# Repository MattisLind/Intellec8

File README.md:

# Intellec8

I bought this Intellec 8/80 on a fleamarket outside Stockholm 30 years ago for the equivalent of ten euros. It has been sitting on a shelf since then and now I got the inspiration to fix it. Before doing anything with the machine I dumed the [firmware](https://github.com/MattisLind/Intellec8/tree/main/EPROMImages) of the EPROMs. 16 1702 EPROM chips. Each of them containing 256 bytes of non-volatile storage. Then I dismantled the entire machine in to pieces and cleaned some 40 years of dust from it. Meanwhile I took quite a lot of photos of the various parts and puth in the [Pictures folder](https://github.com/MattisLind/Intellec8/tree/main/Pictures). 

The first thing to check were the PSU. The Intellec 8 has three PSU assemblies. One provides +5V, another provide +/- 12V and the last one provide -9V and AC for the programming voltage. The -9V supply and the +/- 12V supply worked just fine.

The first thing I tested was the little crowbar addon board. It tripped at almost 9V, a bit to much in my taste, but it was possible to adjust it down to 5.7V. There didn't seemed to be any problems with that other than it was not set correctly.

Then I started working with the PSUs. All off them worked fine except for the +5V PSU that didn't regulate well at all. I had to turn off the crowbare not to make it trip every time. Evverything measured fine, capacitors, carbon composite resistors, forward drop over semiconductor PN-junctions. But it didn't regulate well. Tried to replace the LM723 regulator IC with a NOS IC. But no difference. Then I looked more on the power transistor that acted as a driver for the output stage of the regulator. It was very leaky. With a new power transistor in place the PSU worked fine.

I installed the Front panel controller, CPU and the three memory boards in the backplane and attached the flat cables from the front panel to the front panel controller board and turne the power switch on. There were some kind of activity on the front panel. I could examine and deposit into memory, but RUN mode behaved odd. I wasn't able to single step the CPU but the RUN light could come on. But in RUN mode there were no activity on the FETCH indicator. Strange.

I checked all LEDs on the panel and they seemed to work find as did the switches. To trace problems further I needed to meausure on the front panel controller board. That was quite tricky with the board installed in the backplane. I needed an extender card. So I sat down one Saturday and designed one.

I also inclued test point so it would be easier to attach a logic analyzer if that turned out to be necessary. The more test points the better. And a lot of ground points to be able to attache the ground probes of the LA.

A few weeks later the boards arrived and so did the connector. I choosen a wire-wrap connector which i bent the legs a bit on to make a sturdy connection between the board and the connector.

Now I hade the possibiliy to probe around on the board. The FETCH cycle signal toggled all the time but still the LED was dark. The signal went through a 7417 OC buffer, A3. It turned out that it was always high on the output. A low will cause the LED to be lit. A high will cause it to be turned off. Removed it and tested in my Retro Chip Tester and, yes, it tested bad. A new (date code 1971), tested 7417, was installed and the front panel was a lot happier.

I could enter a short loop at address 0 that was looping back to itself and also single step this little program. Nice!

But when checking the memory at 3800h where the monitor was supposed be located were very strange and did not match the content of the previouslt dumped EPROMs. Pulled out the EPROM board from the backplane and immediatelty saw something that made me suspicous. Two DIP-swicthes. I have had problmes with DIP-switches in the past. And sure enough, closed switches read open-circuit on the meter. Tried to exercise the switches. Tried deoxit, which made it worse. In the end I had to replace them and then with new swicthes in place the memory at 3800h was accessible. I could even start the monitor and saw the LED indicate I/O acces which was likely to be the monitor polling the UART for incoming character.

Now I just have create a current loop adapter and test the I/O card.

## Modifications to support FACIT paper tape reader and punch

```
3639                          .ORG   3639h   
3639   3E FA        RDR:      MVI   A,0FAH   
363B   D3 05                  OUT   5   
363D   DB 05        RLO:      IN    5   
363F   1F                     RAR   
3640   1F                     RAR   
3641   1F                     RAR   
3642   D8                     RC   
3643   17                     RAL   
3644   DA 3D 36               JC    RLO   
3647   DB 04                  IN    4   
3649   F5                     PUSH  PSW   
364A   3E FB                  MVI   A,0FBH   
364C   D3 05                  OUT   5   
364E   DB 05        RHI:      IN    5   
3650   E6 02                  ANI   02H   
3652   CA 4E 36               JZ    RHI   
3655   F1                     POP   PSW   
3656   2F                     CMA   
3657   B7                     ORA   A   
3658   C9                     RET   
3659                PUNCH:    
3659   DB 05                  IN    5   
365B   E6 10                  ANI   010H   
365D   C2 59 36               JNZ   PUNCH   
3660   79                     MOV   A,C   
3661   2F                     CMA   
3662   D3 04                  OUT   4   
3664   3E AF                  MVI   A,0AFH   
3666   D3 05                  OUT   5   
3668   DB 05        HIGH:     IN    5   
366A   E6 10                  ANI   010H   
366C   CA 68 36               JZ    HIGH   
366F   3E BF                  MVI   A,0BFH   
3671   D3 05                  OUT   5   
3673   C9                     RET   
```
Jumptable-locatation at 3010 need change to 59H.

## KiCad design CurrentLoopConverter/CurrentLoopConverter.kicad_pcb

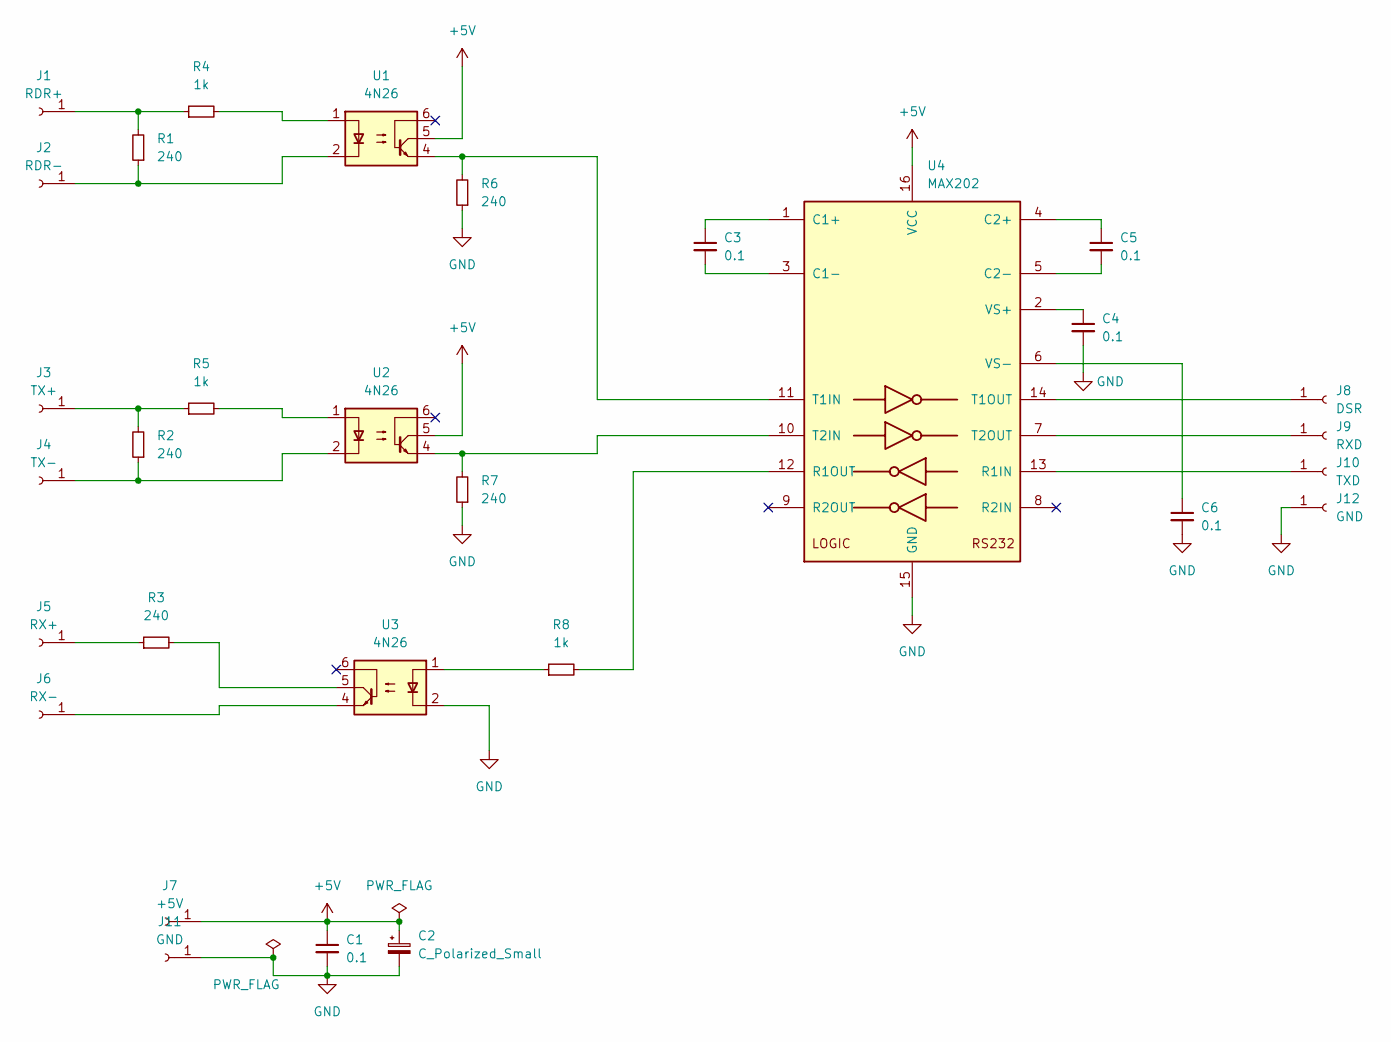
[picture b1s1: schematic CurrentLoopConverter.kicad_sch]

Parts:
C1, C3, C4, C5, C6: 0.1; C_Rect_L7.0mm_W2.0mm_P5.00mm
C2: C_Polarized_Small; CP_Radial_D5.0mm_P2.50mm
J1: RDR+; PinHeader_1x01_P2.54mm_Vertical
J2: RDR-; PinHeader_1x01_P2.54mm_Vertical
J3: TX+; PinHeader_1x01_P2.54mm_Vertical
J4: TX-; PinHeader_1x01_P2.54mm_Vertical
J5: RX+; PinHeader_1x01_P2.54mm_Vertical
J6: RX-; PinHeader_1x01_P2.54mm_Vertical
J7: +5V; PinHeader_1x01_P2.54mm_Vertical
J8: DSR; PinHeader_1x01_P2.54mm_Vertical
J9: RXD; PinHeader_1x01_P2.54mm_Vertical
J10: TXD; PinSocket_1x01_P2.54mm_Vertical
J11, J12: GND; PinHeader_1x01_P2.54mm_Vertical
R1, R2, R3, R6, R7: 240; R_Axial_DIN0207_L6.3mm_D2.5mm_P10.16mm_Horizontal
R4, R5, R8: 1k; R_Axial_DIN0207_L6.3mm_D2.5mm_P10.16mm_Horizontal
U1, U2, U3: 4N26; DIP-6_W7.62mm
U4: MAX202; DIP-16_W7.62mm

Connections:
+5V: C1.1, C2.1, J7.1, U1.5, U2.5, U4.16 (VCC)
GND: C1.2, C2.2, C4.2, C6.2, J11.1, J12.1, R6.1, R7.1, U3.2, U4.15 (GND)
unnamed: C3.1, U4.1 (C1+)
unnamed: C3.2, U4.3 (C1-)
unnamed: C4.1, U4.2 (VS+)
unnamed: C5.1, U4.4 (C2+)
unnamed: C5.2, U4.5 (C2-)
unnamed: C6.1, U4.6 (VS-)
unnamed: J1.1, R1.2, R4.1
unnamed: J2.1, R1.1, U1.2
unnamed: J3.1, R2.2, R5.1
unnamed: J4.1, R2.1, U2.2
unnamed: J5.1, R3.1
unnamed: J6.1, U3.4
unnamed: J8.1, U4.14 (T1OUT)
unnamed: J9.1, U4.7 (T2OUT)
unnamed: J10.1, U4.13 (R1IN)
unnamed: R3.2, U3.5
unnamed: R4.2, U1.1
unnamed: R5.2, U2.1
unnamed: R6.2, U1.4, U4.11 (T1IN)
unnamed: R7.2, U2.4, U4.10 (T2IN)
unnamed: R8.1, U3.1
unnamed: R8.2, U4.12 (R1OUT)

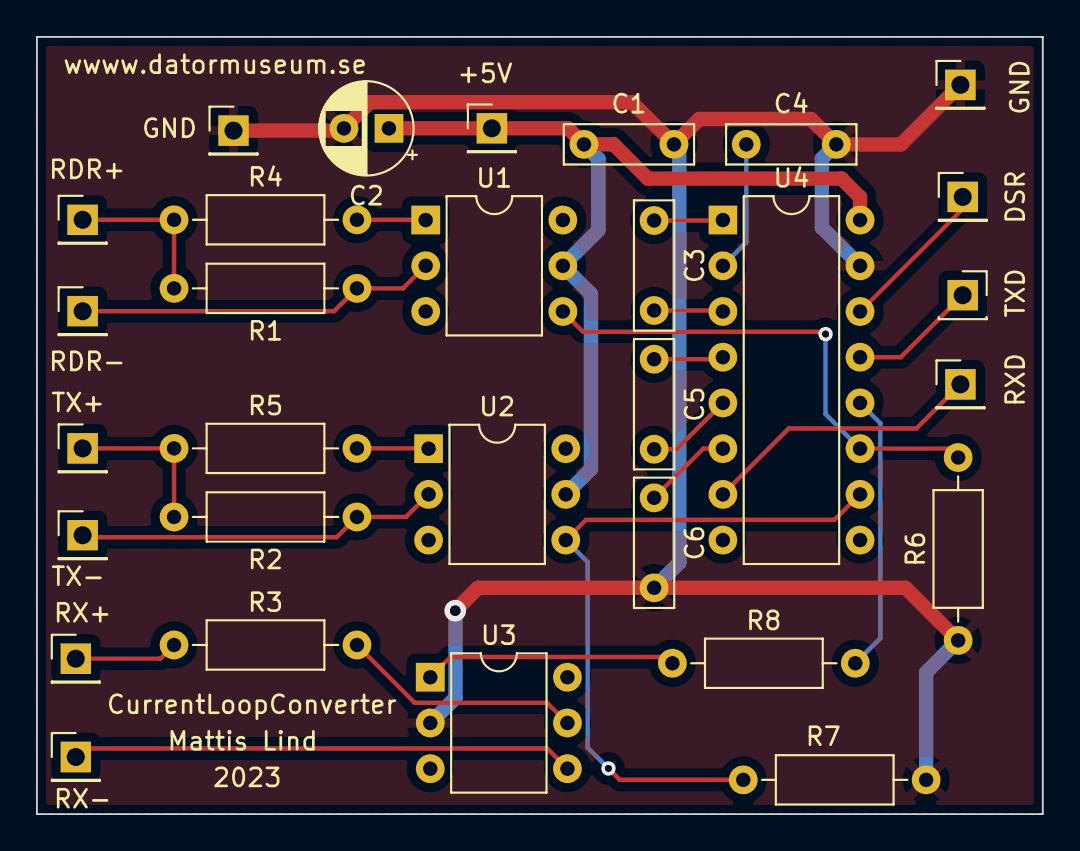
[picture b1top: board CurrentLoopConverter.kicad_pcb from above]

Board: 2 copper layers, 55.9 x 43.2 mm, 30 parts (0 on the bottom side), 24 nets.

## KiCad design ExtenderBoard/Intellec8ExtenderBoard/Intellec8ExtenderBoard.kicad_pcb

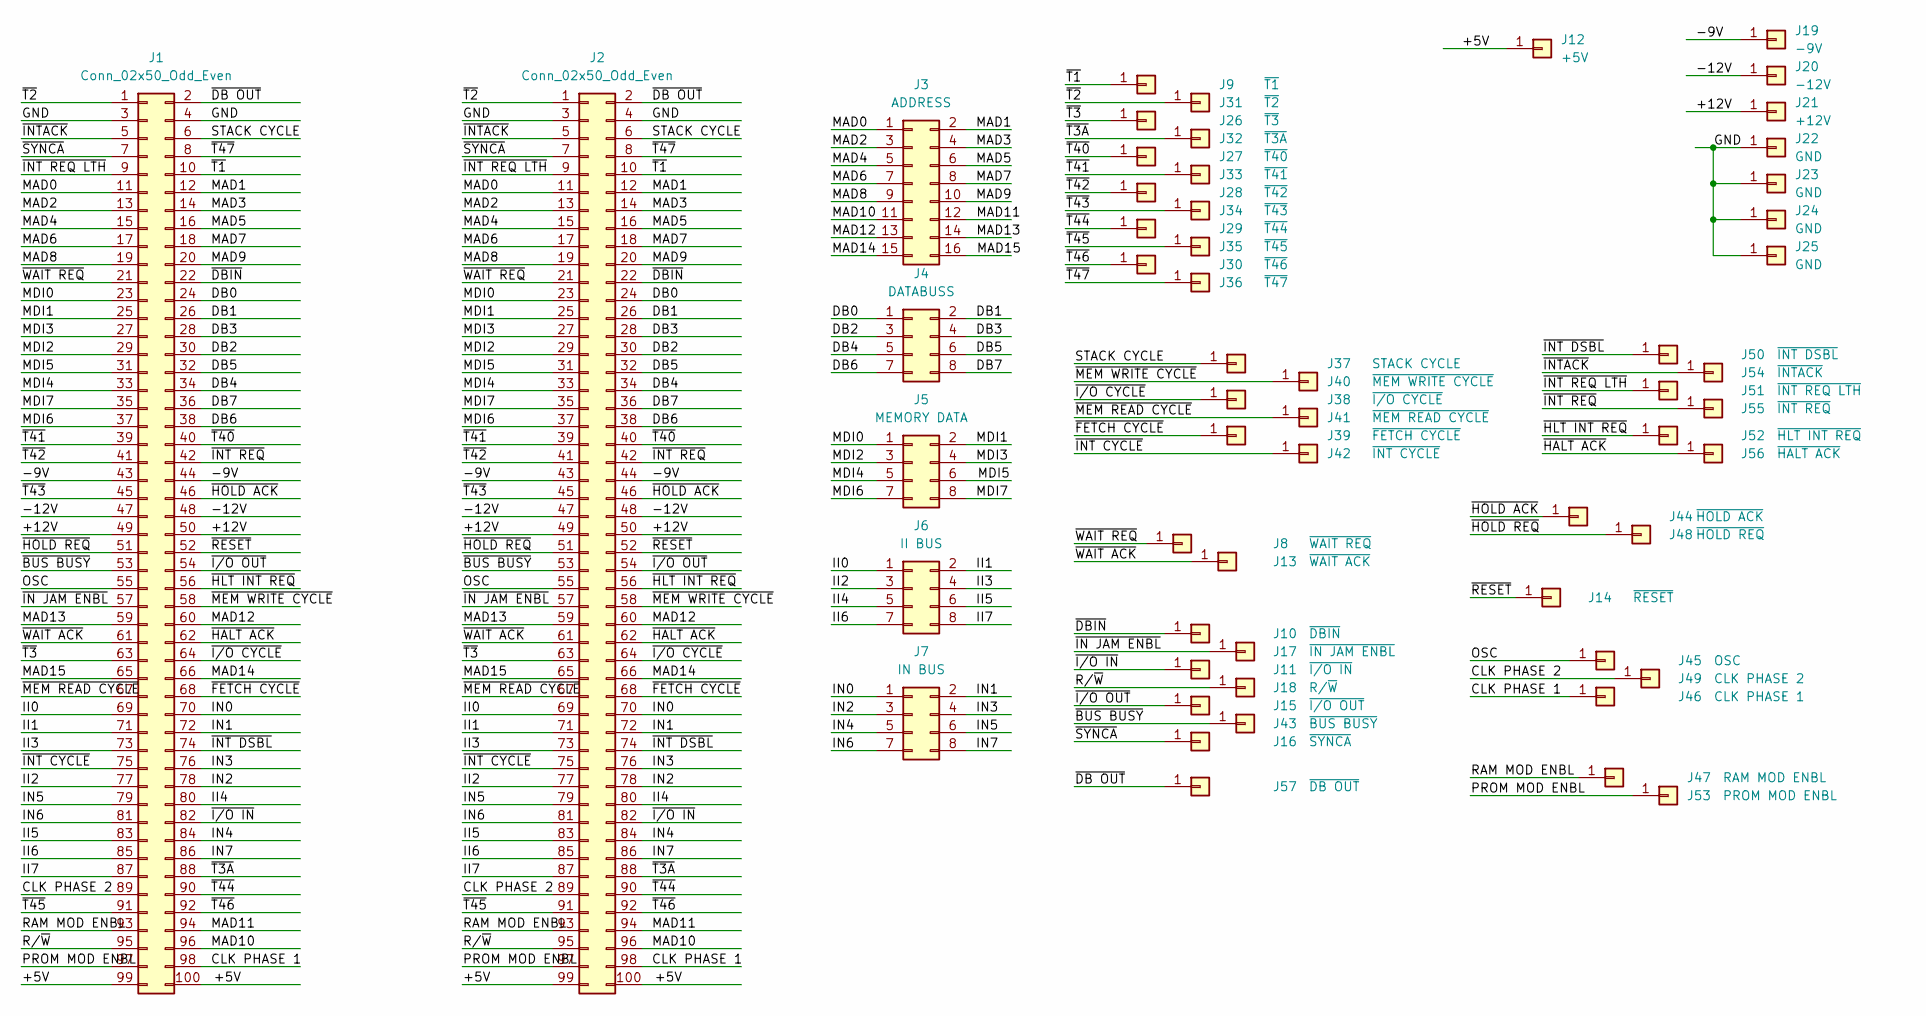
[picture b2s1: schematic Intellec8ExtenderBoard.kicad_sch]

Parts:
J1: Conn_02x50_Odd_Even; INTELLE8
J2: Conn_02x50_Odd_Even; INTELLE8_EXT
J3: ADDRESS; PinHeader_2x08_P2.54mm_Vertical
J4: DATABUSS; PinHeader_2x04_P2.54mm_Vertical
J5: MEMORY DATA; PinHeader_2x04_P2.54mm_Vertical
J6: II BUS; PinHeader_2x04_P2.54mm_Vertical
J7: IN BUS; PinHeader_2x04_P2.54mm_Vertical
J8: ~{WAIT REQ}; PinHeader_1x01_P2.54mm_Vertical
J9: ~{T1}; PinHeader_1x01_P2.54mm_Vertical
J10: ~{DBIN}; PinHeader_1x01_P2.54mm_Vertical
J11: ~{I/O IN}; PinHeader_1x01_P2.54mm_Vertical
J12: +5V; PinHeader_1x01_P2.54mm_Vertical
J13: ~{WAIT ACK}; PinHeader_1x01_P2.54mm_Vertical
J14: ~{RESET}; PinHeader_1x01_P2.54mm_Vertical
J15: ~{I/O OUT}; PinHeader_1x01_P2.54mm_Vertical
J16: ~{SYNCA}; PinHeader_1x01_P2.54mm_Vertical
J17: ~{IN JAM ENBL}; PinHeader_1x01_P2.54mm_Vertical
J18: R/~{W}; PinHeader_1x01_P2.54mm_Vertical
J19: -9V; PinHeader_1x01_P2.54mm_Vertical
J20: -12V; PinHeader_1x01_P2.54mm_Vertical
J21: +12V; PinHeader_1x01_P2.54mm_Vertical
J22, J23, J24, J25: GND; PinHeader_1x01_P2.54mm_Vertical
J26: ~{T3}; PinHeader_1x01_P2.54mm_Vertical
J27: ~{T40}; PinHeader_1x01_P2.54mm_Vertical
J28: ~{T42}; PinHeader_1x01_P2.54mm_Vertical
J29: ~{T44}; PinHeader_1x01_P2.54mm_Vertical
J30: ~{T46}; PinHeader_1x01_P2.54mm_Vertical
J31: ~{T2}; PinHeader_1x01_P2.54mm_Vertical
J32: ~{T3A}; PinHeader_1x01_P2.54mm_Vertical
J33: ~{T41}; PinHeader_1x01_P2.54mm_Vertical
J34: ~{T43}; PinHeader_1x01_P2.54mm_Vertical
J35: ~{T45}; PinHeader_1x01_P2.54mm_Vertical
J36: ~{T47}; PinHeader_1x01_P2.54mm_Vertical
J37: STACK CYCLE; PinHeader_1x01_P2.54mm_Vertical
J38: ~{I/O CYCLE}; PinHeader_1x01_P2.54mm_Vertical
J39: ~{FETCH CYCLE}; PinHeader_1x01_P2.54mm_Vertical
J40: ~{MEM WRITE CYCLE}; PinHeader_1x01_P2.54mm_Vertical
J41: ~{MEM READ CYCLE}; PinHeader_1x01_P2.54mm_Vertical
J42: ~{INT CYCLE}; PinHeader_1x01_P2.54mm_Vertical
J43: ~{BUS BUSY}; PinHeader_1x01_P2.54mm_Vertical
J44: ~{HOLD ACK}; PinHeader_1x01_P2.54mm_Vertical
J45: OSC; PinHeader_1x01_P2.54mm_Vertical
J46: CLK PHASE 1; PinHeader_1x01_P2.54mm_Vertical
J47: RAM MOD ENBL; PinHeader_1x01_P2.54mm_Vertical
J48: ~{HOLD REQ}; PinHeader_1x01_P2.54mm_Vertical
J49: CLK PHASE 2; PinHeader_1x01_P2.54mm_Vertical
J50: ~{INT DSBL}; PinHeader_1x01_P2.54mm_Vertical
J51: ~{INT REQ LTH}; PinHeader_1x01_P2.54mm_Vertical
J52: ~{HLT INT REQ}; PinHeader_1x01_P2.54mm_Vertical
J53: PROM MOD ENBL; PinHeader_1x01_P2.54mm_Vertical
J54: ~{INTACK}; PinHeader_1x01_P2.54mm_Vertical
J55: ~{INT REQ}; PinHeader_1x01_P2.54mm_Vertical
J56: ~{HALT ACK}; PinHeader_1x01_P2.54mm_Vertical
J57: ~{DB OUT}; PinHeader_1x01_P2.54mm_Vertical

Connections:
/+5V: J1.99, J1.100, J2.99, J2.100, J12.1
/+12V: J1.49, J1.50, J2.49, J2.50, J21.1
/-9V: J1.43, J1.44, J2.43, J2.44, J19.1
/-12V: J1.47, J1.48, J2.47, J2.48, J20.1
/CLK PHASE 1: J1.98, J2.98, J46.1
/CLK PHASE 2: J1.89, J2.89, J49.1
/DB0: J1.24, J2.24, J4.1
/DB1: J1.26, J2.26, J4.2
/DB2: J1.30, J2.30, J4.3
/DB3: J1.28, J2.28, J4.4
/DB4: J1.34, J2.34, J4.5
/DB5: J1.32, J2.32, J4.6
/DB6: J1.38, J2.38, J4.7
/DB7: J1.36, J2.36, J4.8
/GND: J1.3, J1.4, J2.3, J2.4, J22.1, J23.1, J24.1, J25.1
/II0: J1.69, J2.69, J6.1
/II1: J1.71, J2.71, J6.2
/II2: J1.77, J2.77, J6.3
/II3: J1.73, J2.73, J6.4
/II4: J1.80, J2.80, J6.5
/II5: J1.83, J2.83, J6.6
/II6: J1.85, J2.85, J6.7
/II7: J1.87, J2.87, J6.8
/IN0: J1.70, J2.70, J7.1
/IN1: J1.72, J2.72, J7.2
/IN2: J1.78, J2.78, J7.3
/IN3: J1.76, J2.76, J7.4
/IN4: J1.84, J2.84, J7.5
/IN5: J1.79, J2.79, J7.6
/IN6: J1.81, J2.81, J7.7
/IN7: J1.86, J2.86, J7.8
/MAD0: J1.11, J2.11, J3.1
/MAD1: J1.12, J2.12, J3.2
/MAD2: J1.13, J2.13, J3.3
/MAD3: J1.14, J2.14, J3.4
/MAD4: J1.15, J2.15, J3.5
/MAD5: J1.16, J2.16, J3.6
/MAD6: J1.17, J2.17, J3.7
/MAD7: J1.18, J2.18, J3.8
/MAD8: J1.19, J2.19, J3.9
/MAD9: J1.20, J2.20, J3.10
/MAD10: J1.96, J2.96, J3.11
/MAD11: J1.94, J2.94, J3.12
/MAD12: J1.60, J2.60, J3.13
/MAD13: J1.59, J2.59, J3.14
/MAD14: J1.66, J2.66, J3.15
/MAD15: J1.65, J2.65, J3.16
/MDI0: J1.23, J2.23, J5.1
/MDI1: J1.25, J2.25, J5.2
/MDI2: J1.29, J2.29, J5.3
/MDI3: J1.27, J2.27, J5.4
/MDI4: J1.33, J2.33, J5.5
/MDI5: J1.31, J2.31, J5.6
/MDI6: J1.37, J2.37, J5.7
/MDI7: J1.35, J2.35, J5.8
/OSC: J1.55, J2.55, J45.1
/PROM MOD ENBL: J1.97, J2.97, J53.1
/RAM MOD ENBL: J1.93, J2.93, J47.1
/R/~W: J1.95, J2.95, J18.1
/STACK CYCLE: J1.6, J2.6, J37.1
/~BUS BUSY: J1.53, J2.53, J43.1
/~DB OUT: J1.2, J2.2, J57.1
/~DBIN: J1.22, J2.22, J10.1
/~FETCH CYCLE: J1.68, J2.68, J39.1
/~HALT ACK: J1.62, J2.62, J56.1
/~HLT INT REQ: J1.56, J2.56, J52.1
/~HOLD ACK: J1.46, J2.46, J44.1
/~HOLD REQ: J1.51, J2.51, J48.1
/~IN JAM ENBL: J1.57, J2.57, J17.1
/~INT CYCLE: J1.75, J2.75, J42.1
/~INT DSBL: J1.74, J2.74, J50.1
/~INT REQ LTH: J1.9, J2.9, J51.1
/~INT REQ: J1.42, J2.42, J55.1
/~INTACK: J1.5, J2.5, J54.1
/~I/O CYCLE: J1.64, J2.64, J38.1
/~I/O IN: J1.82, J2.82, J11.1
/~I/O OUT: J1.54, J2.54, J15.1
/~MEM READ CYCLE: J1.67, J2.67, J41.1
/~MEM WRITE CYCLE: J1.58, J2.58, J40.1
/~RESET: J1.52, J2.52, J14.1
/~SYNCA: J1.7, J2.7, J16.1
/~T1: J1.10, J2.10, J9.1
/~T2: J1.1, J2.1, J31.1
/~T3A: J1.88, J2.88, J32.1
/~T3: J1.63, J2.63, J26.1
/~T40: J1.40, J2.40, J27.1
/~T41: J1.39, J2.39, J33.1
/~T42: J1.41, J2.41, J28.1
/~T43: J1.45, J2.45, J34.1
/~T44: J1.90, J2.90, J29.1
/~T45: J1.91, J2.91, J35.1
/~T46: J1.92, J2.92, J30.1
/~T47: J1.8, J2.8, J36.1
/~WAIT ACK: J1.61, J2.61, J13.1
/~WAIT REQ: J1.21, J2.21, J8.1

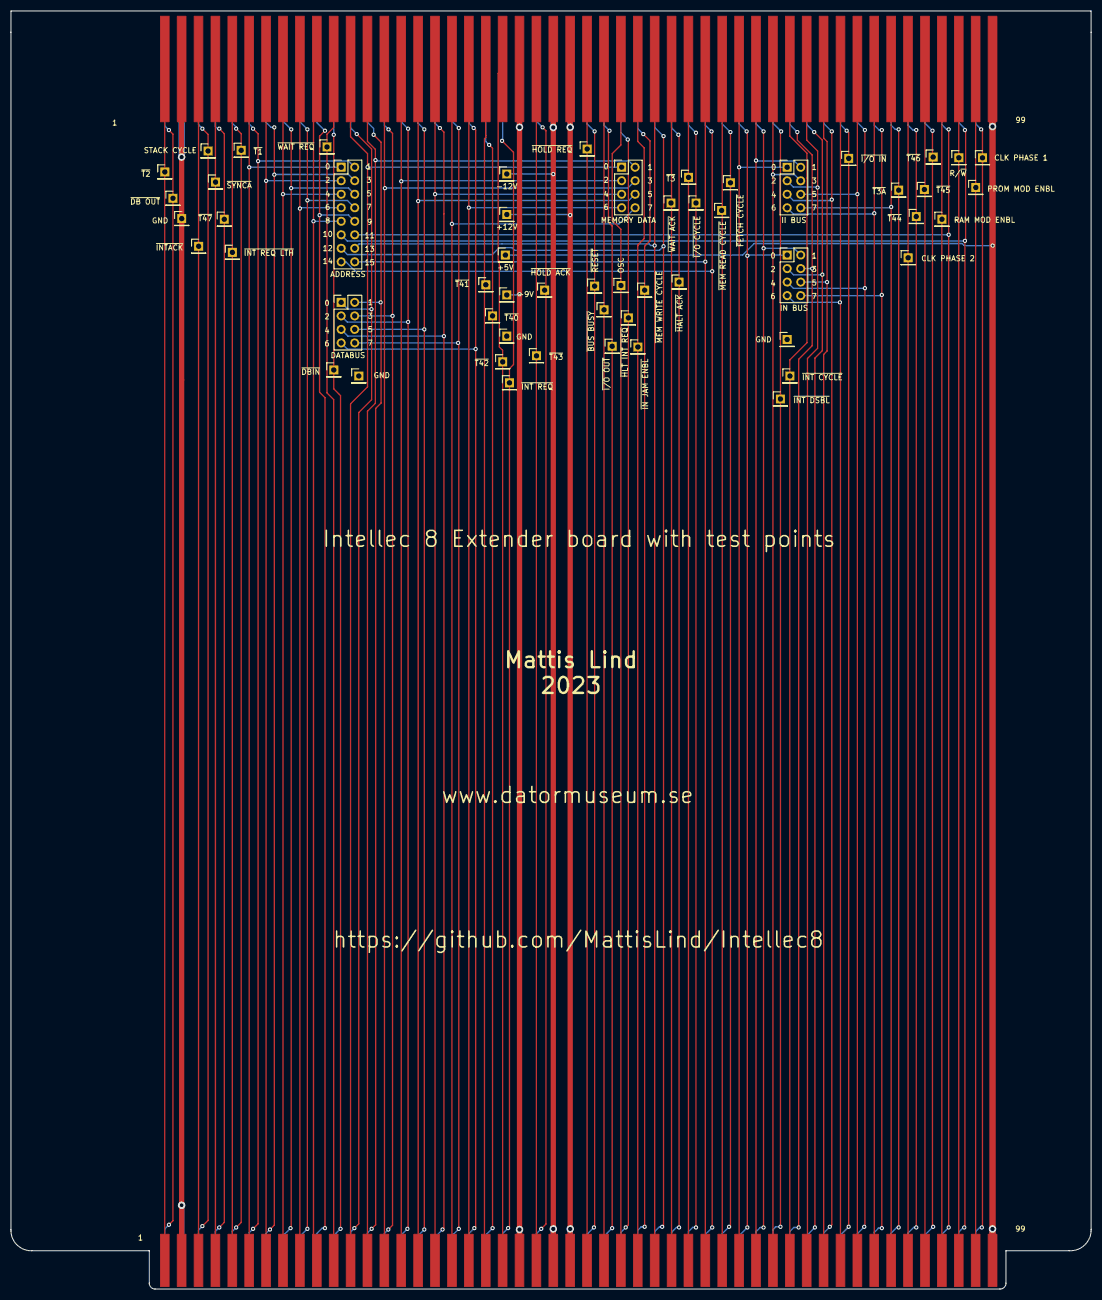
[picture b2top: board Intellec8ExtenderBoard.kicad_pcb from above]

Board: 2 copper layers, 203.0 x 240.2 mm, 57 parts (0 on the bottom side), 95 nets.

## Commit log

2023-02-10 Added extender board and all other files.
2023-02-11 Upated the README
2023-02-11 Added a design for a current loop interface for the Intellec 8
2023-06-01 Added info on mods
2024-10-02 Adding code for testing 4070 and 4021
